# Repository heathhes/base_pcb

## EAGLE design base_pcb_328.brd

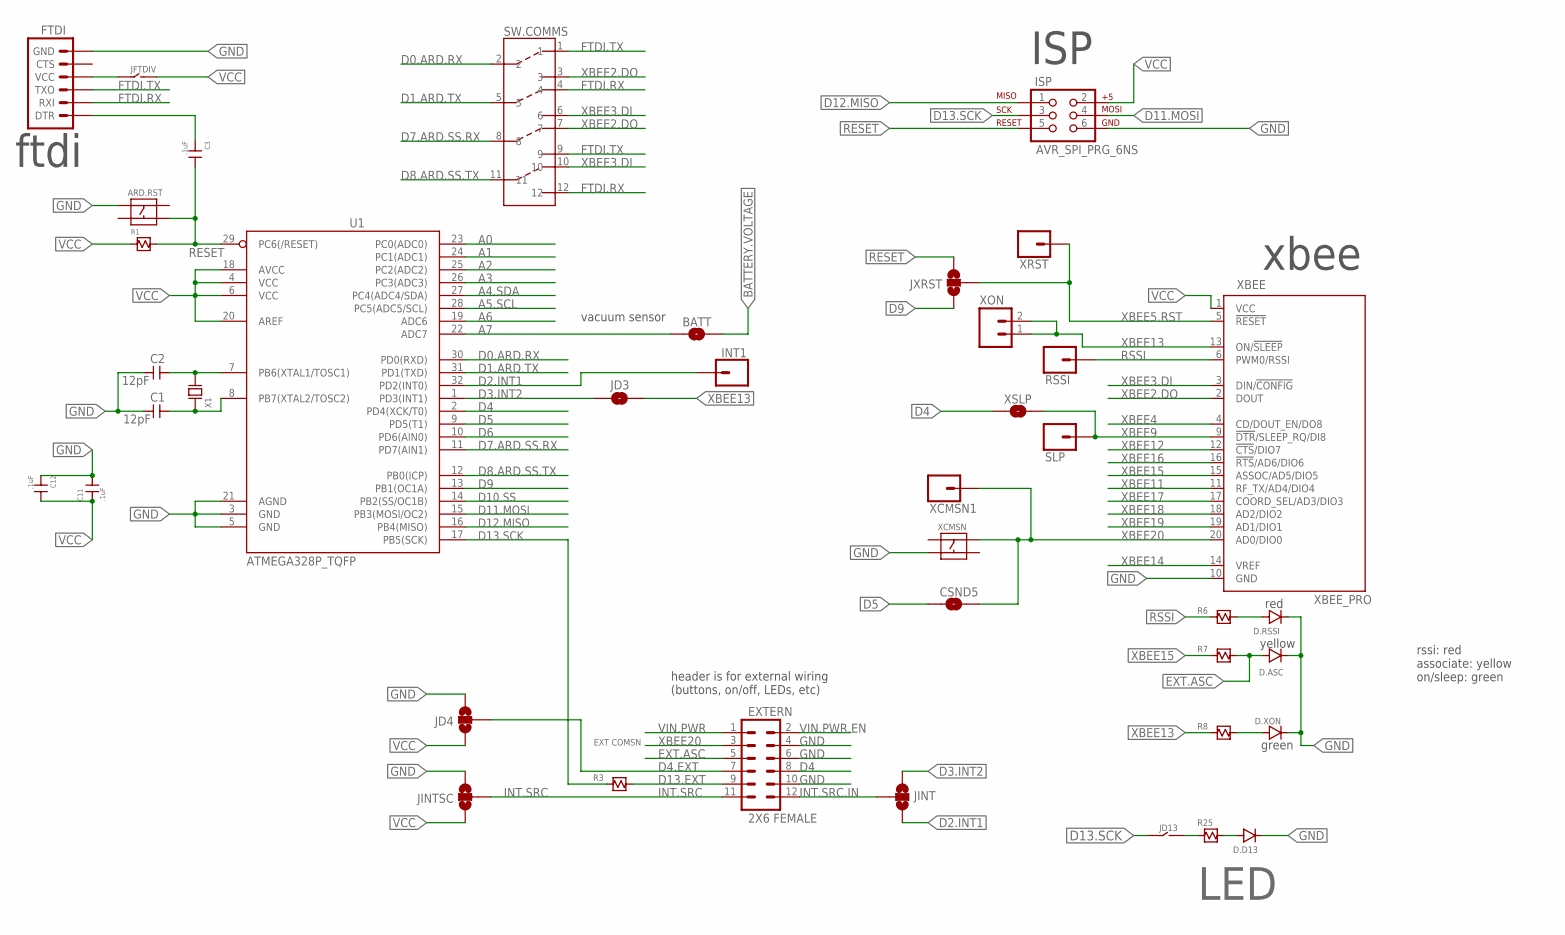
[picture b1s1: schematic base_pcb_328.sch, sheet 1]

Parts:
ARD.RST: C&K_PUSHBUTTON_SMALL_MOM_SPST_SMD; C&K_PUSHBUTTON_MOM_SMALL_SPST_SMD
BATT: JUMPER-PAD-2-NOYES_SILK; PAD-JUMPER-2-NO_YES_SILK
C1, C2: 12pF; 0603_CAPACITOR
C3: .1uF; 0603_CAPACITOR
C11, C12: .1uF; 0402_CAPACITOR
CSND5: JUMPER-PAD-2-NOYES_SILK; PAD-JUMPER-2-NO_YES_SILK
D.ASC, D.D13, D.RSSI, D.XON: 0603_LED
EXTERN: 2X6 FEMALE; 2X6
FTDI: ARDUINO_SERIAL_PROGRAMPTH; 1X06
INT1: M01PTH; 1X01
ISP: AVR_SPI_PRG_6NS; 2X3-NS
JD3: JUMPER-PAD-2-NOYES_SILK; PAD-JUMPER-2-NO_YES_SILK
JD4: JUMPER-PAD-3-NOYES_SILK; PAD-JUMPER-3-NO_YES_SILK
JD13: JUMPER_2WAY_.1"_TH
JFTDIV: JUMPER_2WAY_.1"_TH
JINT: JUMPER-PAD-3-NOYES_SILK; PAD-JUMPER-3-NO_YES_SILK
JINTSC: JUMPER-PAD-3-NOYES_SILK; PAD-JUMPER-3-NO_YES_SILK
JXRST: JUMPER-PAD-3-NOYES_SILK; PAD-JUMPER-3-NO_YES_SILK
R1, R3, R6, R7, R8, R25: 0603_RESISTOR
RSSI: M01PTH; 1X01
SLP: M01PTH; 1X01
SW.COMMS: COPAL_4PDT_SLIDE_SWITCH_TH; COPAL_4PDT_SLIDE_SWITCH
U1: ATMEGA328P_TQFP; TQFP32-08
X1: ABRACON_ABM3-16.000MHZ-D2Y-T_OSCILLATOR
XBEE: XBEE_PRO
XCMSN: C&K_PUSHBUTTON_SMALL_MOM_SPST_SMD; C&K_PUSHBUTTON_MOM_SMALL_SPST_SMD
XCMSN1: M01PTH; 1X01
XON: M02PTH; 1X02
XRST: M01PTH; 1X01
XSLP: JUMPER-PAD-2-NOYES_SILK; PAD-JUMPER-2-NO_YES_SILK

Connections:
A0: U1.23 (PC0(ADC0)); also elsewhere on the board
A1: U1.24 (PC1(ADC1)); also elsewhere on the board
A2: U1.25 (PC2(ADC2)); also elsewhere on the board
A3: U1.26 (PC3(ADC3)); also elsewhere on the board
A4.SDA: U1.27 (PC4(ADC4/SDA)); also elsewhere on the board
A5.SCL: U1.28 (PC5(ADC5/SCL)); also elsewhere on the board
A6: U1.19 (ADC6); also elsewhere on the board
A7: BATT.1, U1.22 (ADC7)
BATTERY.VOLTAGE: BATT.2; also elsewhere on the board
D0.ARD.RX: SW.COMMS.2, U1.30 (PD0(RXD))
D1.ARD.TX: SW.COMMS.5, U1.31 (PD1(TXD))
D2.INT1: INT1.1, JINT.3, U1.32 (PD2(INT0)); also elsewhere on the board
D3.INT2: JD3.1, JINT.1, U1.1 (PD3(INT1)); also elsewhere on the board
D4: EXTERN.8, U1.2 (PD4(XCK/T0)), XSLP.1; also elsewhere on the board
D4.EXT: EXTERN.7, JD4.2
D5: CSND5.1, U1.9 (PD5(T1)); also elsewhere on the board
D6: U1.10 (PD6(AIN0)); also elsewhere on the board
D7.ARD.SS.RX: SW.COMMS.8, U1.11 (PD7(AIN1))
D8.ARD.SS.TX: SW.COMMS.11, U1.12 (PB0(ICP)); also elsewhere on the board
D9: JXRST.1, U1.13 (PB1(OC1A)); also elsewhere on the board
D10.SS: U1.14 (PB2(SS/OC1B)); also elsewhere on the board
D11.MOSI: ISP.4, U1.15 (PB3(MOSI/OC2)); also elsewhere on the board
D12.MISO: ISP.1, U1.16 (PB4(MISO)); also elsewhere on the board
D13.EXT: EXTERN.9, R3.2
D13.SCK: ISP.3, JD13.P$1, R3.1, U1.17 (PB5(SCK)); also elsewhere on the board
EXT.ASC: D.ASC.1, EXTERN.5, R7.2
FTDI.RX: FTDI.2 (RXI), SW.COMMS.4, SW.COMMS.12
FTDI.TX: FTDI.3 (TXO), SW.COMMS.1, SW.COMMS.9
GND: ARD.RST.1, C1.2, C2.2, C11.2, C12.1, D.ASC.2, D.D13.2, D.RSSI.2, D.XON.2, EXTERN.4, EXTERN.6, EXTERN.10, FTDI.6 (GND), ISP.6, JD4.3, JINTSC.3, U1.3 (GND), U1.5 (GND), U1.21 (AGND), XBEE.10 (GND), XCMSN.3; also elsewhere on the board
INT.SRC: EXTERN.11, JINTSC.2
INT.SRC.IN: EXTERN.12, JINT.2
unnamed: C2.1, U1.7 (PB6(XTAL1/TOSC1)), X1.P$2 (2)
unnamed: C1.1, U1.8 (PB7(XTAL2/TOSC2)), X1.P$1 (1)
unnamed: C3.1, FTDI.1 (DTR)
unnamed: D.D13.1, R25.2
unnamed: JD13.P$2, R25.1
unnamed: D.RSSI.1, R6.2
unnamed: D.XON.1, R8.2
RESET: ARD.RST.4, C3.2, ISP.5, JXRST.3, R1.2, U1.29 (PC6(/RESET))
RSSI: R6.1, RSSI.1, XBEE.6 (PWM0/RSSI); also elsewhere on the board
VCC: C11.1, C12.2, ISP.2, JD4.1, JFTDIV.P$2, JINTSC.1, R1.1, U1.4 (VCC), U1.6 (VCC), U1.18 (AVCC), U1.20 (AREF), XBEE.1 (VCC); also elsewhere on the board
VCC.FTDI: FTDI.4 (VCC), JFTDIV.P$1
VIN.PWR: EXTERN.1; also elsewhere on the board
VIN.PWR.EN: EXTERN.2; also elsewhere on the board
XBEE2.DO: SW.COMMS.3, SW.COMMS.7, XBEE.2 (DOUT); also elsewhere on the board
XBEE3.DI: SW.COMMS.6, SW.COMMS.10, XBEE.3 (DIN/!CONFIG); also elsewhere on the board
XBEE4: XBEE.4 (CD/DOUT_EN/DO8); also elsewhere on the board
XBEE5.RST: JXRST.2, XBEE.5 (!RESET), XRST.1; also elsewhere on the board
XBEE9: SLP.1, XBEE.9 (!DTR!/SLEEP_RQ/DI8), XSLP.2; also elsewhere on the board
XBEE11: XBEE.11 (RF_TX/AD4/DIO4); also elsewhere on the board
XBEE12: XBEE.12 (!CTS!/DIO7); also elsewhere on the board
XBEE13: JD3.2, R8.1, XBEE.13 (ON/!SLEEP), XON.1, XON.2; also elsewhere on the board
XBEE14: XBEE.14 (VREF); also elsewhere on the board
XBEE15: R7.1, XBEE.15 (ASSOC/AD5/DIO5); also elsewhere on the board
XBEE16: XBEE.16 (!RTS!/AD6/DIO6); also elsewhere on the board
XBEE17: XBEE.17 (COORD_SEL/AD3/DIO3); also elsewhere on the board
XBEE18: XBEE.18 (AD2/DIO2); also elsewhere on the board
XBEE19: XBEE.19 (AD1/DIO1); also elsewhere on the board
XBEE20: CSND5.2, EXTERN.3, XBEE.20 (AD0/DIO0), XCMSN.2, XCMSN1.1; also elsewhere on the board

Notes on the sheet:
ISP
xbee
ftdi
vacuum sensor
LED
rssi: red associate: yellow on/sleep: green
red
green
yellow
header is for external wiring (buttons, on/off, LEDs, etc)
EXT COMSN

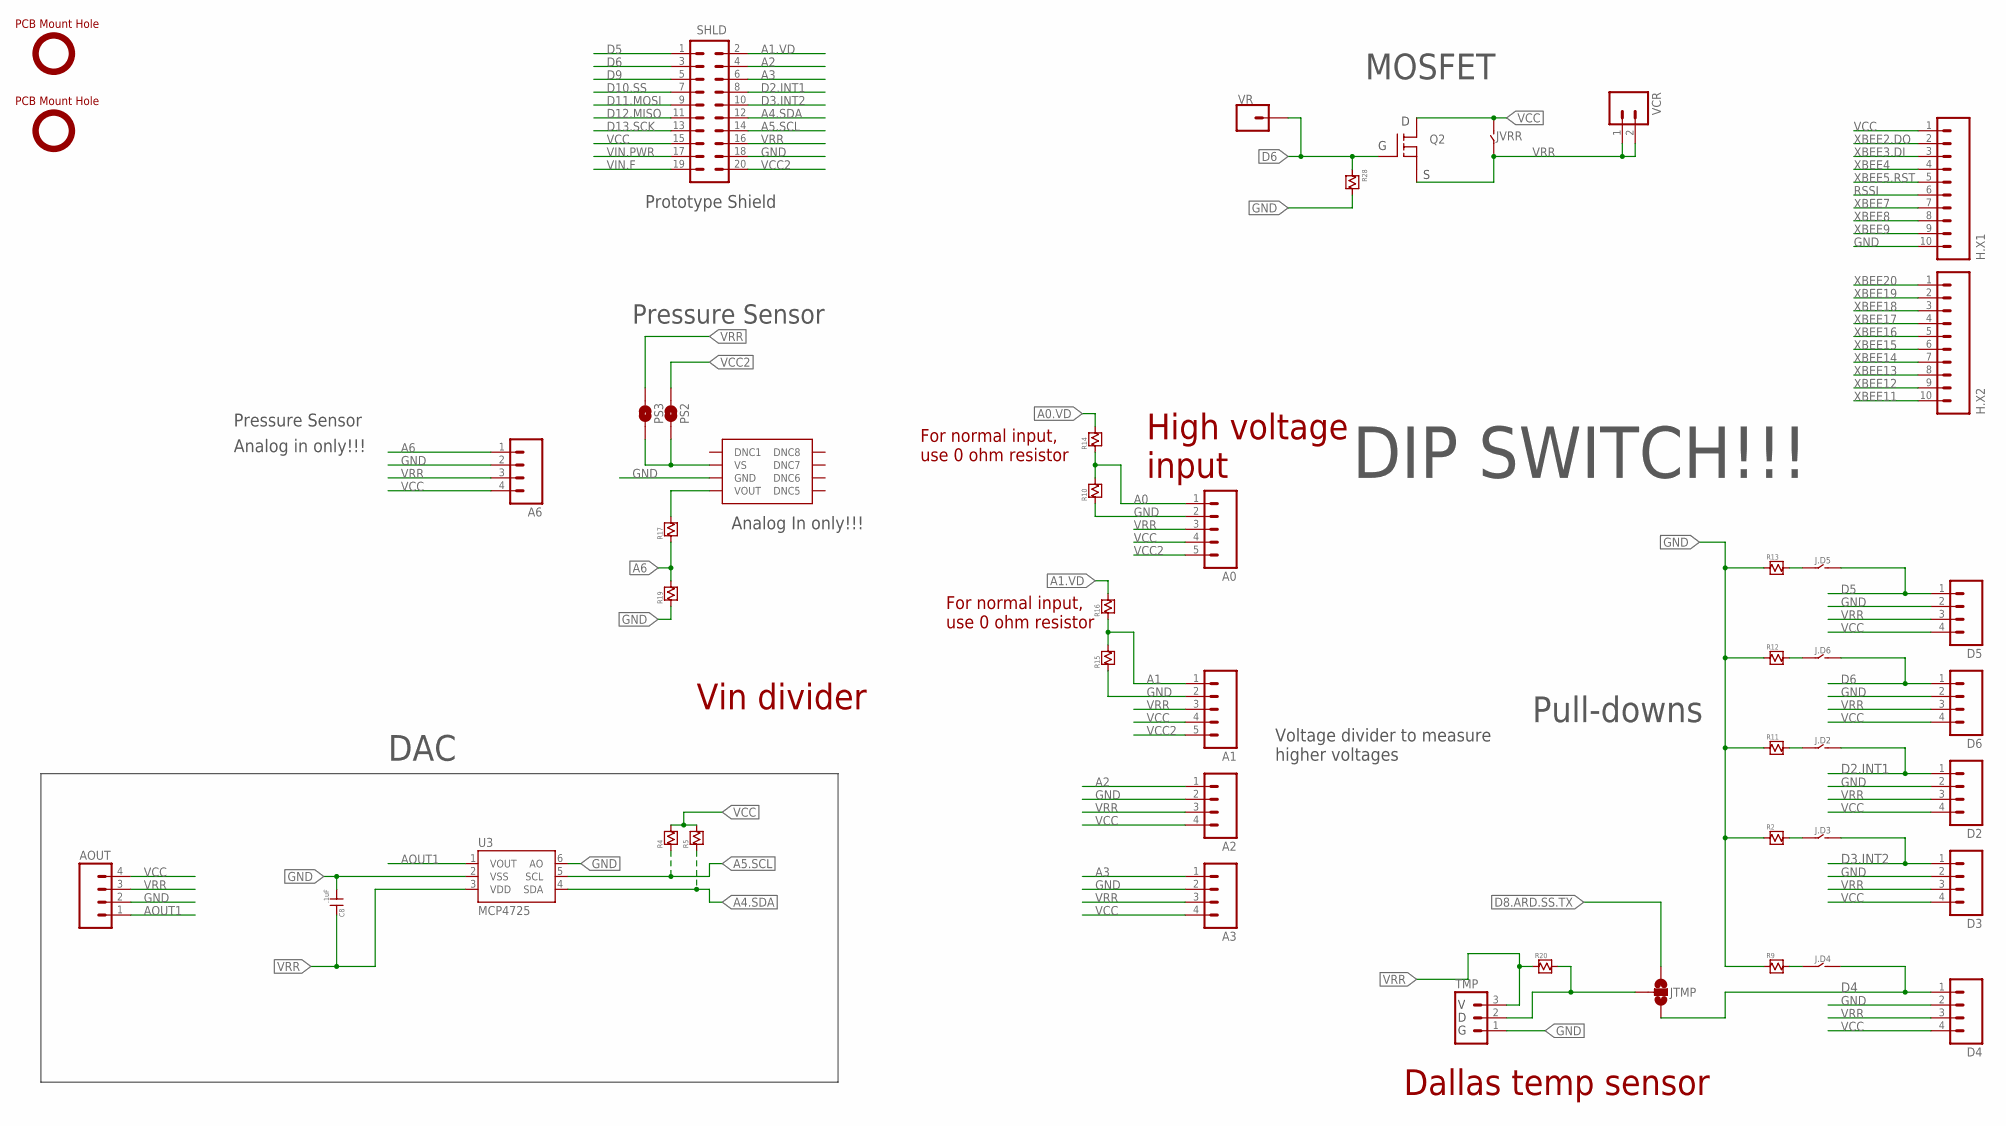
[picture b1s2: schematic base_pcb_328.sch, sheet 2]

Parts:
A0, A1: M05PTH; 1X05
A2, A3, A6: M04PTH; 1X04
AOUT: M04PTH; 1X04
C8: .1uF; 0603_CAPACITOR
D2, D3, D4, D5, D6: M04PTH; 1X04
H.X1, H.X2: M10NO_SILK_PTH_FEMALE; 1X10_NO_SILK
J.D2, J.D3, J.D4, J.D5, J.D6: JUMPER_2WAY_.1"_TH
JTMP: JUMPER-PAD-3-NOYES_SILK; PAD-JUMPER-3-NO_YES_SILK
JVRR: JUMPER_2WAY_.1"_TH
PS2, PS3: JUMPER-PAD-2-NOYES_SILK; PAD-JUMPER-2-NO_YES_SILK
Q2: INFINEON_MOSFET_NCH; INFINEON_MOSFET_NCH_SMD
R2, R4, R5, R9, R10, R11, R12, R13, R14, R15, R16, R17, R19, R20, R28: 0603_RESISTOR
SHLD: M10X2; 2X10
TMP: M03PTH; 1X03
U3: MCP4725; SOT23-6
U$9: MPXV6115VC6U
U$13, U$14: PCB_HOLE
VCR: M02PTH; 1X02
VR: M01PTH; 1X01

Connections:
A0: A0.1, R10.2, R14.1; also elsewhere on the board
A0.VD: R14.2; also elsewhere on the board
A1: A1.1, R15.2, R16.1; also elsewhere on the board
A1.VD: R16.2, SHLD.2
A2: A2.1, SHLD.4; also elsewhere on the board
A3: A3.1, SHLD.6; also elsewhere on the board
A4.SDA: R5.1, SHLD.12, U3.4 (SDA); also elsewhere on the board
A5.SCL: R4.1, SHLD.14, U3.5 (SCL); also elsewhere on the board
A6: A6.1, R17.1, R19.2; also elsewhere on the board
A6.IN: R17.2, U$9.4 (VOUT)
AOUT1: AOUT.1, U3.1 (VOUT)
D2.INT1: D2.1, J.D2.P$2, SHLD.8; also elsewhere on the board
D3.INT2: D3.1, J.D3.P$2, SHLD.10; also elsewhere on the board
D4: D4.1, J.D4.P$2, JTMP.3; also elsewhere on the board
D5: D5.1, J.D5.P$2, SHLD.1; also elsewhere on the board
D6: D6.1, J.D6.P$2, Q2.G, R28.1, SHLD.3, VR.1; also elsewhere on the board
D8.ARD.SS.TX: JTMP.1; also elsewhere on the board
D9: SHLD.5; also elsewhere on the board
D10.SS: SHLD.7; also elsewhere on the board
D11.MOSI: SHLD.9; also elsewhere on the board
D12.MISO: SHLD.11; also elsewhere on the board
D13.SCK: SHLD.13; also elsewhere on the board
GND: A0.2, A1.2, A2.2, A3.2, A6.2, AOUT.2, C8.1, D2.2, D3.2, D4.2, D5.2, D6.2, H.X1.10, R2.1, R9.1, R10.1, R11.1, R12.1, R13.1, R15.1, R19.1, R28.2, SHLD.18, TMP.1, U3.2 (VSS), U3.6 (AO), U$9.3 (GND); also elsewhere on the board
unnamed: JTMP.2, R20.2, TMP.2
unnamed: PS2.1, PS3.1, U$9.2 (VS)
unnamed: J.D3.P$1, R2.2
unnamed: J.D6.P$1, R12.2
unnamed: J.D5.P$1, R13.2
unnamed: J.D2.P$1, R11.2
unnamed: J.D4.P$1, R9.2
RSSI: H.X1.6; also elsewhere on the board
VCC: A0.4, A1.4, A2.4, A3.4, A6.4, AOUT.4, D2.4, D3.4, D4.4, D5.4, D6.4, H.X1.1, JVRR.P$2, Q2.D, R4.2, R5.2, SHLD.15; also elsewhere on the board
VCC2: A0.5, A1.5, PS2.2, SHLD.20; also elsewhere on the board
VIN.F: SHLD.19; also elsewhere on the board
VIN.PWR: SHLD.17; also elsewhere on the board
VRR: A0.3, A1.3, A2.3, A3.3, A6.3, AOUT.3, C8.2, D2.3, D3.3, D4.3, D5.3, D6.3, JVRR.P$1, PS3.2, Q2.S, R20.1, SHLD.16, TMP.3, U3.3 (VDD), VCR.1, VCR.2; also elsewhere on the board
XBEE2.DO: H.X1.2; also elsewhere on the board
XBEE3.DI: H.X1.3; also elsewhere on the board
XBEE4: H.X1.4; also elsewhere on the board
XBEE5.RST: H.X1.5; also elsewhere on the board
XBEE7: H.X1.7
XBEE8: H.X1.8
XBEE9: H.X1.9; also elsewhere on the board
XBEE11: H.X2.10; also elsewhere on the board
XBEE12: H.X2.9; also elsewhere on the board
XBEE13: H.X2.8; also elsewhere on the board
XBEE14: H.X2.7; also elsewhere on the board
XBEE15: H.X2.6; also elsewhere on the board
XBEE16: H.X2.5; also elsewhere on the board
XBEE17: H.X2.4; also elsewhere on the board
XBEE18: H.X2.3; also elsewhere on the board
XBEE19: H.X2.2; also elsewhere on the board
XBEE20: H.X2.1; also elsewhere on the board

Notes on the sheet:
MOSFET
DAC
Analog In only!!!
Prototype Shield
Pressure Sensor
Voltage divider to measure higher voltages
Analog in only!!!
Pull-downs
Dallas temp sensor
Vin divider
High voltage input
For normal input, use 0 ohm resistor
DIP SWITCH!!!

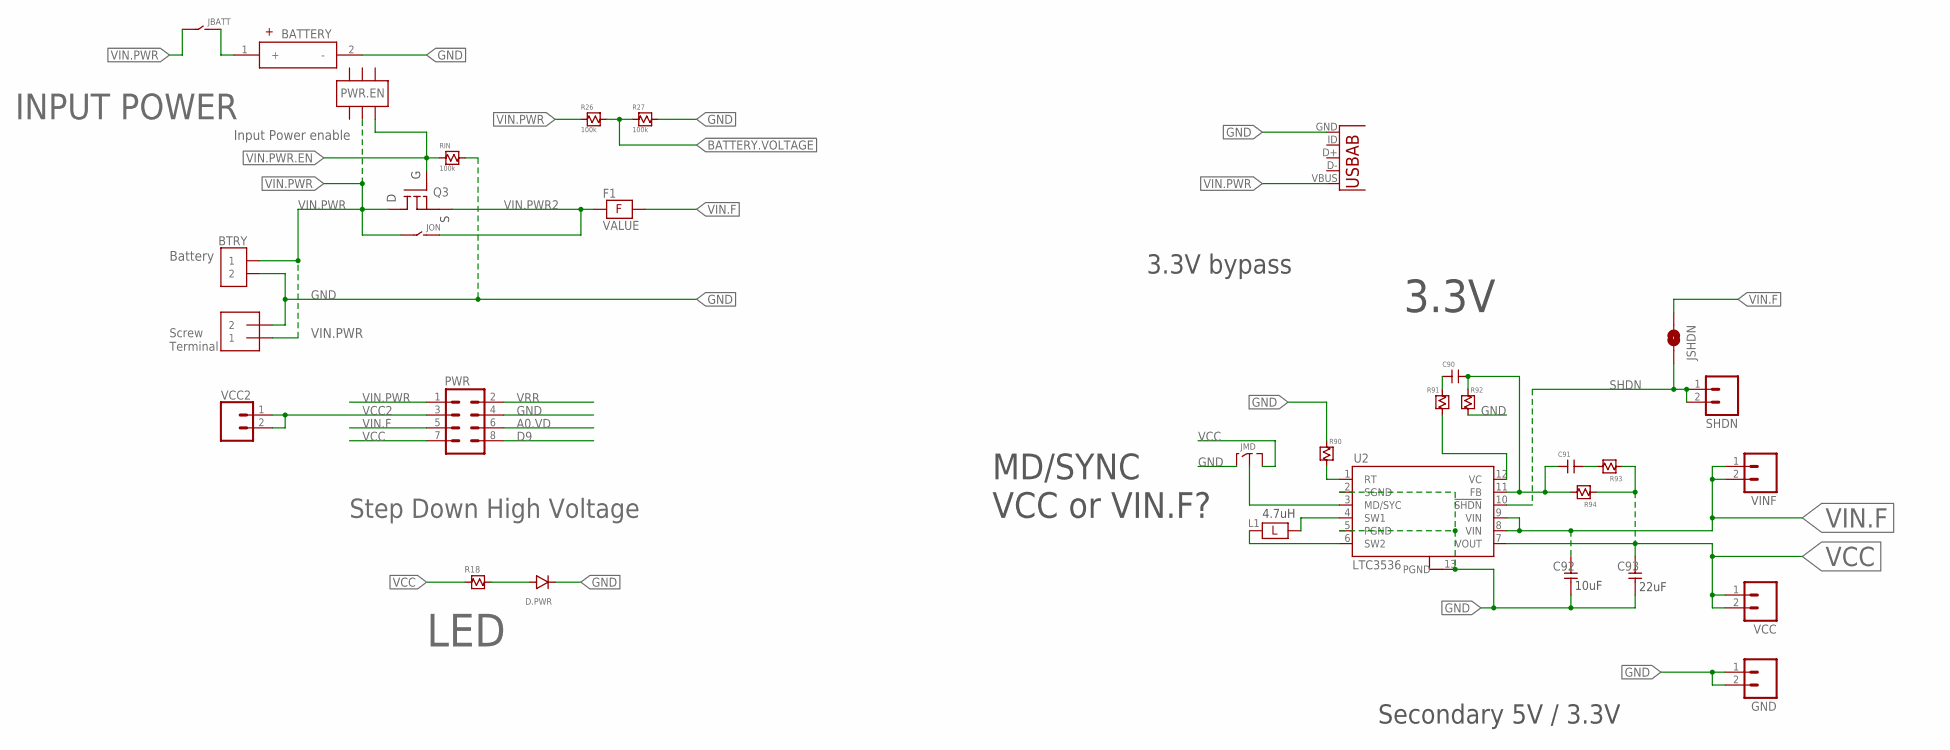
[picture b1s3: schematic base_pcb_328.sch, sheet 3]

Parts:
5V: USB-AB; USB-AB-MICRO-SMD
BATTERY: BATTERY_HOLDER_18650
BTRY: MOLEX_2PIN_LOCKING_TH
C90, C91: 0603_CAPACITOR
C92: 10uF; 0805_CAPACITOR
C93: 22uF; 0805_CAPACITOR
D.PWR: 0603_LED
F1: PTC_FUSE_PTC_1206; BEL_FUSE_PTC_FUSE_1206
GND: M02PTH; 1X02
INPUT.PWR: 1X2-3.5MM
JBATT: JUMPER_2WAY_.1"_TH
JMD: JUMPER_3WAY_.1"_TH
JON: JUMPER_2WAY_.1"_TH
JSHDN: JUMPER-PAD-2-NOYES_SILK; PAD-JUMPER-2-NO_YES_SILK
L1: 4.7uH; BOURNS_INDUCTOR_SMD
PWR: M04X2; 2X4
PWR.EN: C&K_DPDT_SLIDE_SWITCH_SMD_HIDDEN_PADS; C&K_SLIDE_SWITCH_DPDT_SMD_HIDDEN_PADS
Q3: INFINEON_MOSFET_NCH; INFINEON_MOSFET_NCH_SMD
R18, R90, R91, R92, R93, R94: 0603_RESISTOR
R26, R27: 100k; 0603_RESISTOR
RIN: 100k; 0603_RESISTOR
SHDN: M02PTH; 1X02
U2: LTC3536_ADJ_12PIN
VCC, VCC2: M02PTH; 1X02
VINF: M02PTH; 1X02

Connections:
A0.VD: PWR.6; also elsewhere on the board
BATTERY.VOLTAGE: R26.2, R27.1; also elsewhere on the board
D9: PWR.8; also elsewhere on the board
GND: 5V.GND, BATTERY.2 (-), BTRY.2, C92.1, C93.1, D.PWR.2, GND.1, GND.2, INPUT.PWR.2, JMD.P$3, PWR.4, R27.2, R90.2, R92.1, RIN.2, U2.2 (SGND), U2.5 (PGND), U2.13 (PGND); also elsewhere on the board
unnamed: BATTERY.1 (+), JBATT.P$2
unnamed: L1.P$2, U2.4 (SW1)
unnamed: D.PWR.1, R18.2
unnamed: L1.P$1, U2.6 (SW2)
unnamed: R90.1, U2.1 (RT)
unnamed: C90.2, C91.1, R92.2, R94.2, U2.11 (FB)
unnamed: C90.1, R91.2
unnamed: R91.1, U2.12 (VC)
unnamed: C91.2, R93.2
unnamed: JMD.P$2, U2.3 (MD/SYC)
SHDN: JSHDN.2, SHDN.1, SHDN.2, U2.10 (!SHDN)
VCC: C93.2, JMD.P$1, PWR.7, R18.1, R93.1, R94.1, U2.7 (VOUT), VCC.1, VCC.2; also elsewhere on the board
VCC2: PWR.3, VCC2.1, VCC2.2; also elsewhere on the board
VIN.F: C92.2, F1.P$2, JSHDN.1, PWR.5, U2.8 (VIN), U2.9 (VIN), VINF.1, VINF.2; also elsewhere on the board
VIN.PWR: 5V.VBUS, BTRY.1, INPUT.PWR.1, JBATT.P$1, JON.P$1, PWR.1, PWR.EN.5, Q3.D, R26.1; also elsewhere on the board
VIN.PWR2: F1.P$1, JON.P$2, Q3.S
VIN.PWR.EN: PWR.EN.4, Q3.G, RIN.1; also elsewhere on the board
VRR: PWR.2; also elsewhere on the board

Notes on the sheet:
4.7uH
INPUT POWER
Battery
Input Power enable
Screw Terminal
Step Down High Voltage
LED
3.3V
3.3V bypass
Secondary 5V / 3.3V
MD/SYNC VCC or VIN.F?
BATTERY

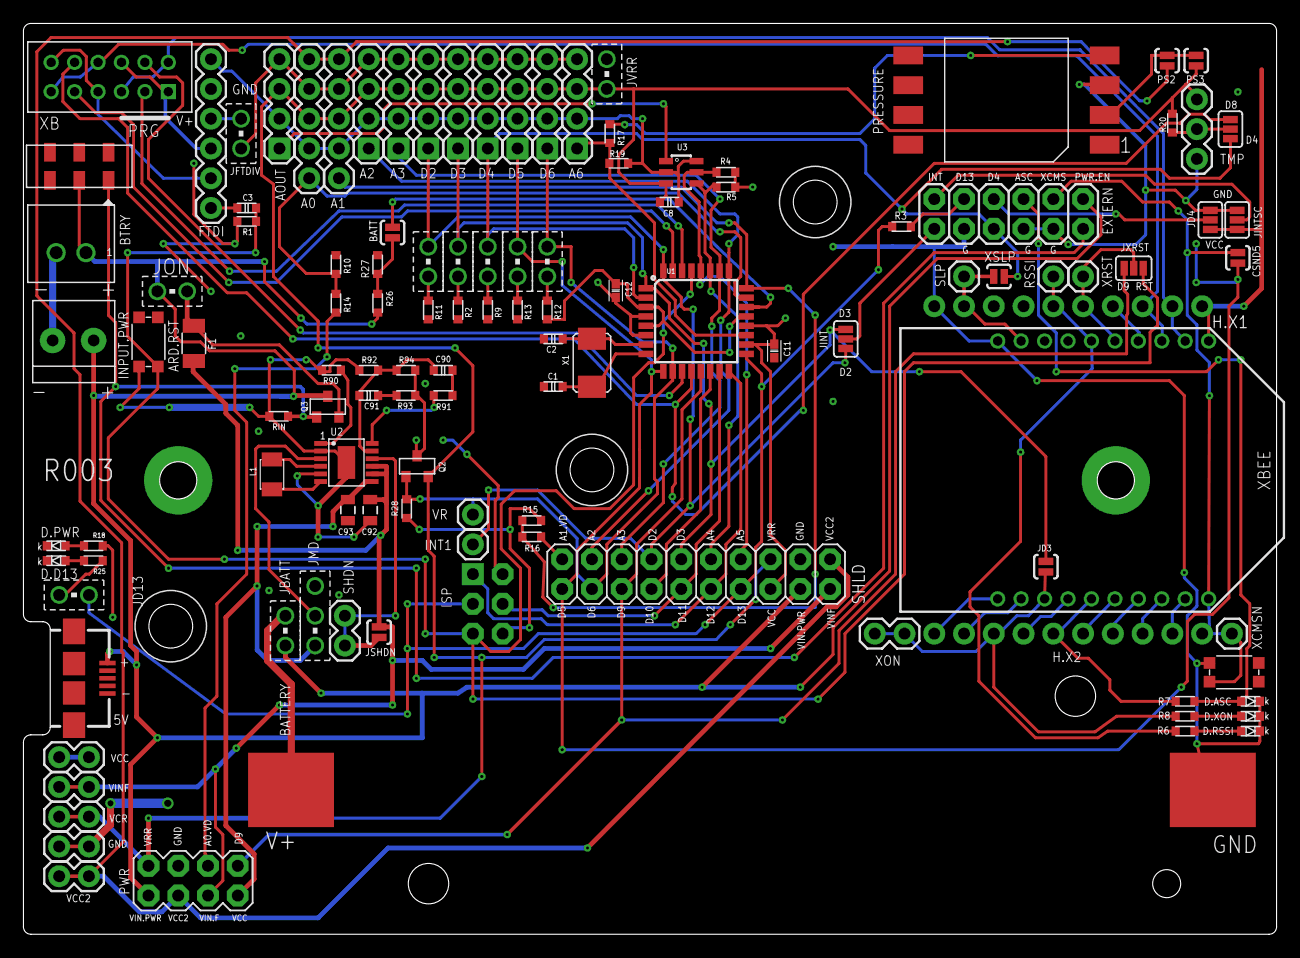
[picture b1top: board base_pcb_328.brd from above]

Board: 2 copper layers, 106.9 x 77.7 mm, 123 parts (0 on the bottom side), 85 nets.

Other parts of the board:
U$1: POLYCASE_WH_02
U$2: PEM_2-56
U$8: BASE328_SHIELD_1

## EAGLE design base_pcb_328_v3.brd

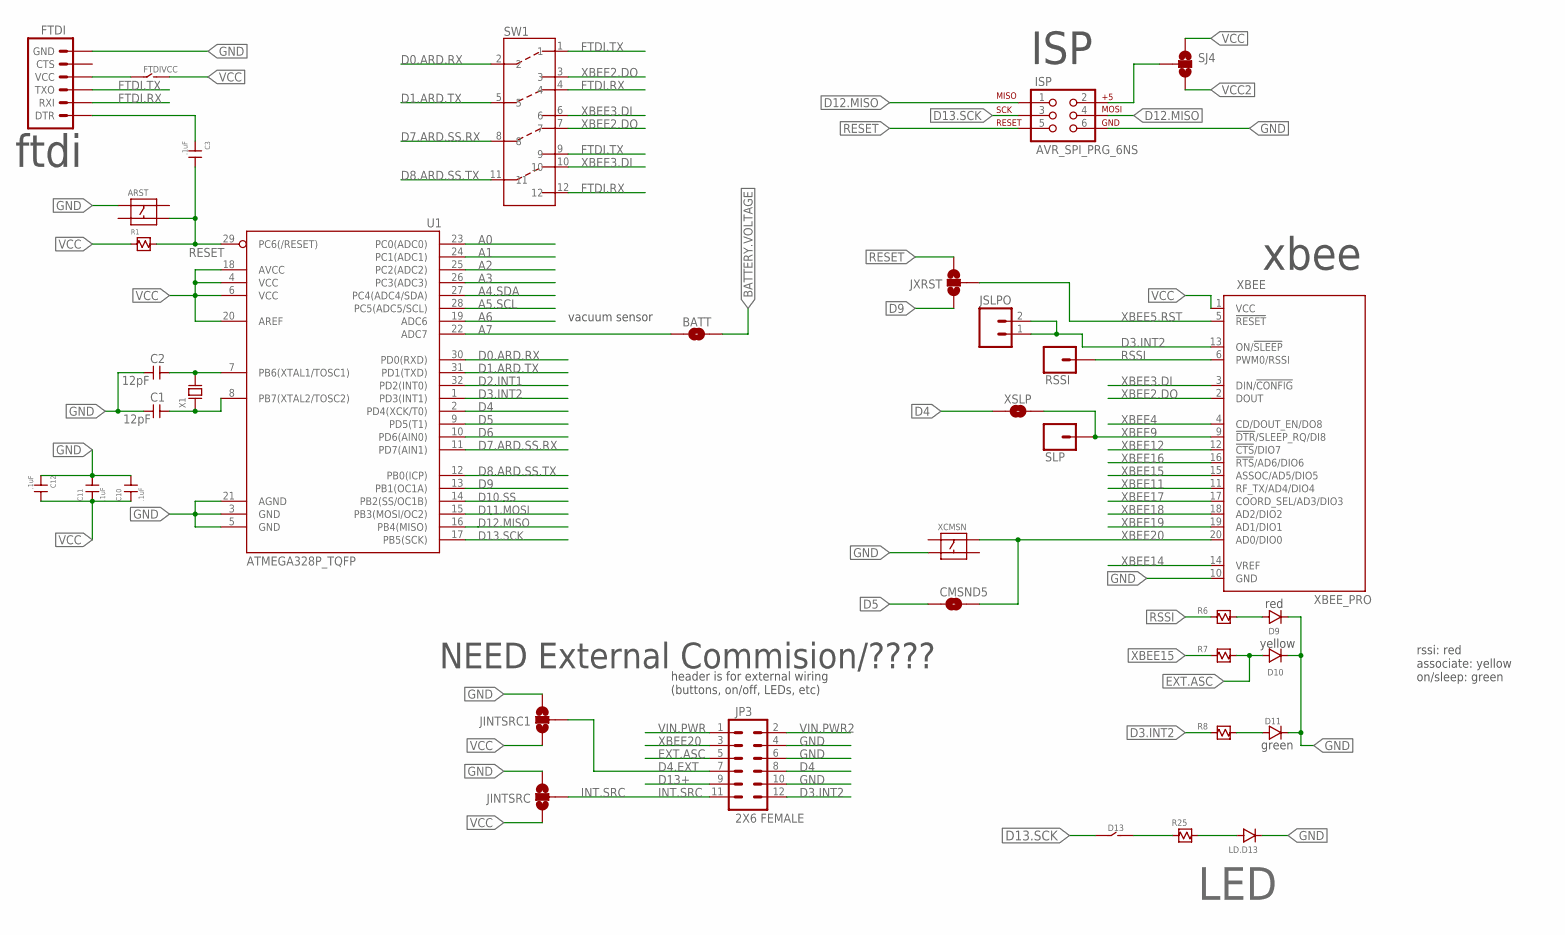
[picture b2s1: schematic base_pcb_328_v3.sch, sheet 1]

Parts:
ARST: C&K_PUSHBUTTON_SMALL_MOM_SPST_SMD; C&K_PUSHBUTTON_MOM_SMALL_SPST_SMD
BATT: JUMPER-PAD-2-NOYES_SILK; PAD-JUMPER-2-NO_YES_SILK
C1, C2: 12pF; 0603_CAPACITOR
C3: .1uF; 0603_CAPACITOR
C10, C11, C12: .1uF; 0402_CAPACITOR
CMSND5: JUMPER-PAD-2-NOYES_SILK; PAD-JUMPER-2-NO_YES_SILK
D9, D10, D11: 0603_LED
D13: JUMPER_2WAY_.1"_TH
FTDI: ARDUINO_SERIAL_PROGRAMPTH; 1X06
FTDIVCC: JUMPER_2WAY_.1"_TH
ISP: AVR_SPI_PRG_6NS; 2X3-NS
JINTSRC, JINTSRC1: JUMPER-PAD-3-NOYES_SILK; PAD-JUMPER-3-NO_YES_SILK
JP3: 2X6 FEMALE; 2X6
JSLPO: M02PTH; 1X02
JXRST: JUMPER-PAD-3-NOYES_SILK; PAD-JUMPER-3-NO_YES_SILK
LD.D13: 0603_LED
R1, R6, R7, R8, R25: 0603_RESISTOR
RSSI: M01PTH; 1X01
SJ4: JUMPER-PAD-3-NOYES_SILK; PAD-JUMPER-3-NO_YES_SILK
SLP: M01PTH; 1X01
SW1: COPAL_4PDT_SLIDE_SWITCH_TH; COPAL_4PDT_SLIDE_SWITCH
U1: ATMEGA328P_TQFP; TQFP32-08
X1: ABRACON_ABM3-16.000MHZ-D2Y-T_OSCILLATOR
XBEE: XBEE_PRO
XCMSN: C&K_PUSHBUTTON_SMALL_MOM_SPST_SMD; C&K_PUSHBUTTON_MOM_SMALL_SPST_SMD
XSLP: JUMPER-PAD-2-NOYES_SILK; PAD-JUMPER-2-NO_YES_SILK

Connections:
A0: U1.23 (PC0(ADC0)); also elsewhere on the board
A1: U1.24 (PC1(ADC1)); also elsewhere on the board
A2: U1.25 (PC2(ADC2)); also elsewhere on the board
A3: U1.26 (PC3(ADC3)); also elsewhere on the board
A4.SDA: U1.27 (PC4(ADC4/SDA)); also elsewhere on the board
A5.SCL: U1.28 (PC5(ADC5/SCL)); also elsewhere on the board
A6: U1.19 (ADC6); also elsewhere on the board
A7: BATT.1, U1.22 (ADC7)
BATTERY.VOLTAGE: BATT.2; also elsewhere on the board
D0.ARD.RX: SW1.2, U1.30 (PD0(RXD))
D1.ARD.TX: SW1.5, U1.31 (PD1(TXD))
D2.INT1: U1.32 (PD2(INT0)); also elsewhere on the board
D3.INT2: JP3.12, JSLPO.1, JSLPO.2, R8.1, U1.1 (PD3(INT1)), XBEE.13 (ON/!SLEEP); also elsewhere on the board
D4: JP3.8, U1.2 (PD4(XCK/T0)), XSLP.1; also elsewhere on the board
D4.EXT: JINTSRC1.2, JP3.7
D5: CMSND5.1, U1.9 (PD5(T1)); also elsewhere on the board
D6: U1.10 (PD6(AIN0)); also elsewhere on the board
D7.ARD.SS.RX: SW1.8, U1.11 (PD7(AIN1))
D8.ARD.SS.TX: SW1.11, U1.12 (PB0(ICP))
D9: JXRST.1, U1.13 (PB1(OC1A)); also elsewhere on the board
D10.SS: U1.14 (PB2(SS/OC1B)); also elsewhere on the board
D11.MOSI: U1.15 (PB3(MOSI/OC2)); also elsewhere on the board
D12.MISO: ISP.1, ISP.4, U1.16 (PB4(MISO)); also elsewhere on the board
D13+: JP3.9
D13.SCK: D13.P$1, ISP.3, U1.17 (PB5(SCK)); also elsewhere on the board
EXT.ASC: D10.1, JP3.5, R7.2
FTDI.RX: FTDI.2 (RXI)
FTDI.TX: FTDI.3 (TXO)
GND: ARST.1, C1.2, C2.2, C10.2, C11.2, C12.1, D9.2, D10.2, D11.2, FTDI.6 (GND), ISP.6, JINTSRC.3, JINTSRC1.3, JP3.4, JP3.6, JP3.10, LD.D13.2, U1.3 (GND), U1.5 (GND), U1.21 (AGND), XBEE.10 (GND), XCMSN.3; also elsewhere on the board
INT.SRC: JINTSRC.2, JP3.11
unnamed: C2.1, U1.7 (PB6(XTAL1/TOSC1)), X1.P$2 (2)
unnamed: C1.1, U1.8 (PB7(XTAL2/TOSC2)), X1.P$1 (1)
unnamed: C3.1, FTDI.1 (DTR)
unnamed: LD.D13.1, R25.2
unnamed: D13.P$2, R25.1
unnamed: ISP.2, SJ4.2
unnamed: D9.1, R6.2
unnamed: D11.1, R8.2
RESET: ARST.4, C3.2, ISP.5, JXRST.3, R1.2, U1.29 (PC6(/RESET))
RSSI: R6.1, RSSI.1, XBEE.6 (PWM0/RSSI); also elsewhere on the board
VCC: C10.1, C11.1, C12.2, FTDI.4 (VCC), FTDIVCC.P$1, FTDIVCC.P$2, JINTSRC.1, JINTSRC1.1, R1.1, SJ4.1, U1.4 (VCC), U1.6 (VCC), U1.18 (AVCC), U1.20 (AREF), XBEE.1 (VCC); also elsewhere on the board
VCC2: SJ4.3; also elsewhere on the board
VIN.PWR: JP3.1; also elsewhere on the board
VIN.PWR2: JP3.2; also elsewhere on the board
XBEE2.DO: XBEE.2 (DOUT); also elsewhere on the board
XBEE3.DI: XBEE.3 (DIN/!CONFIG); also elsewhere on the board
XBEE4: XBEE.4 (CD/DOUT_EN/DO8); also elsewhere on the board
XBEE5.RST: JXRST.2, XBEE.5 (!RESET); also elsewhere on the board
XBEE9: SLP.1, XBEE.9 (!DTR!/SLEEP_RQ/DI8), XSLP.2; also elsewhere on the board
XBEE11: XBEE.11 (RF_TX/AD4/DIO4); also elsewhere on the board
XBEE12: XBEE.12 (!CTS!/DIO7); also elsewhere on the board
XBEE14: XBEE.14 (VREF); also elsewhere on the board
XBEE15: R7.1, XBEE.15 (ASSOC/AD5/DIO5); also elsewhere on the board
XBEE16: XBEE.16 (!RTS!/AD6/DIO6); also elsewhere on the board
XBEE17: XBEE.17 (COORD_SEL/AD3/DIO3); also elsewhere on the board
XBEE18: XBEE.18 (AD2/DIO2); also elsewhere on the board
XBEE19: XBEE.19 (AD1/DIO1); also elsewhere on the board
XBEE20: CMSND5.2, JP3.3, XBEE.20 (AD0/DIO0), XCMSN.2; also elsewhere on the board

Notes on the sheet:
ISP
xbee
ftdi
vacuum sensor
LED
rssi: red associate: yellow on/sleep: green
red
green
yellow
header is for external wiring (buttons, on/off, LEDs, etc)
NEED External Commision/????

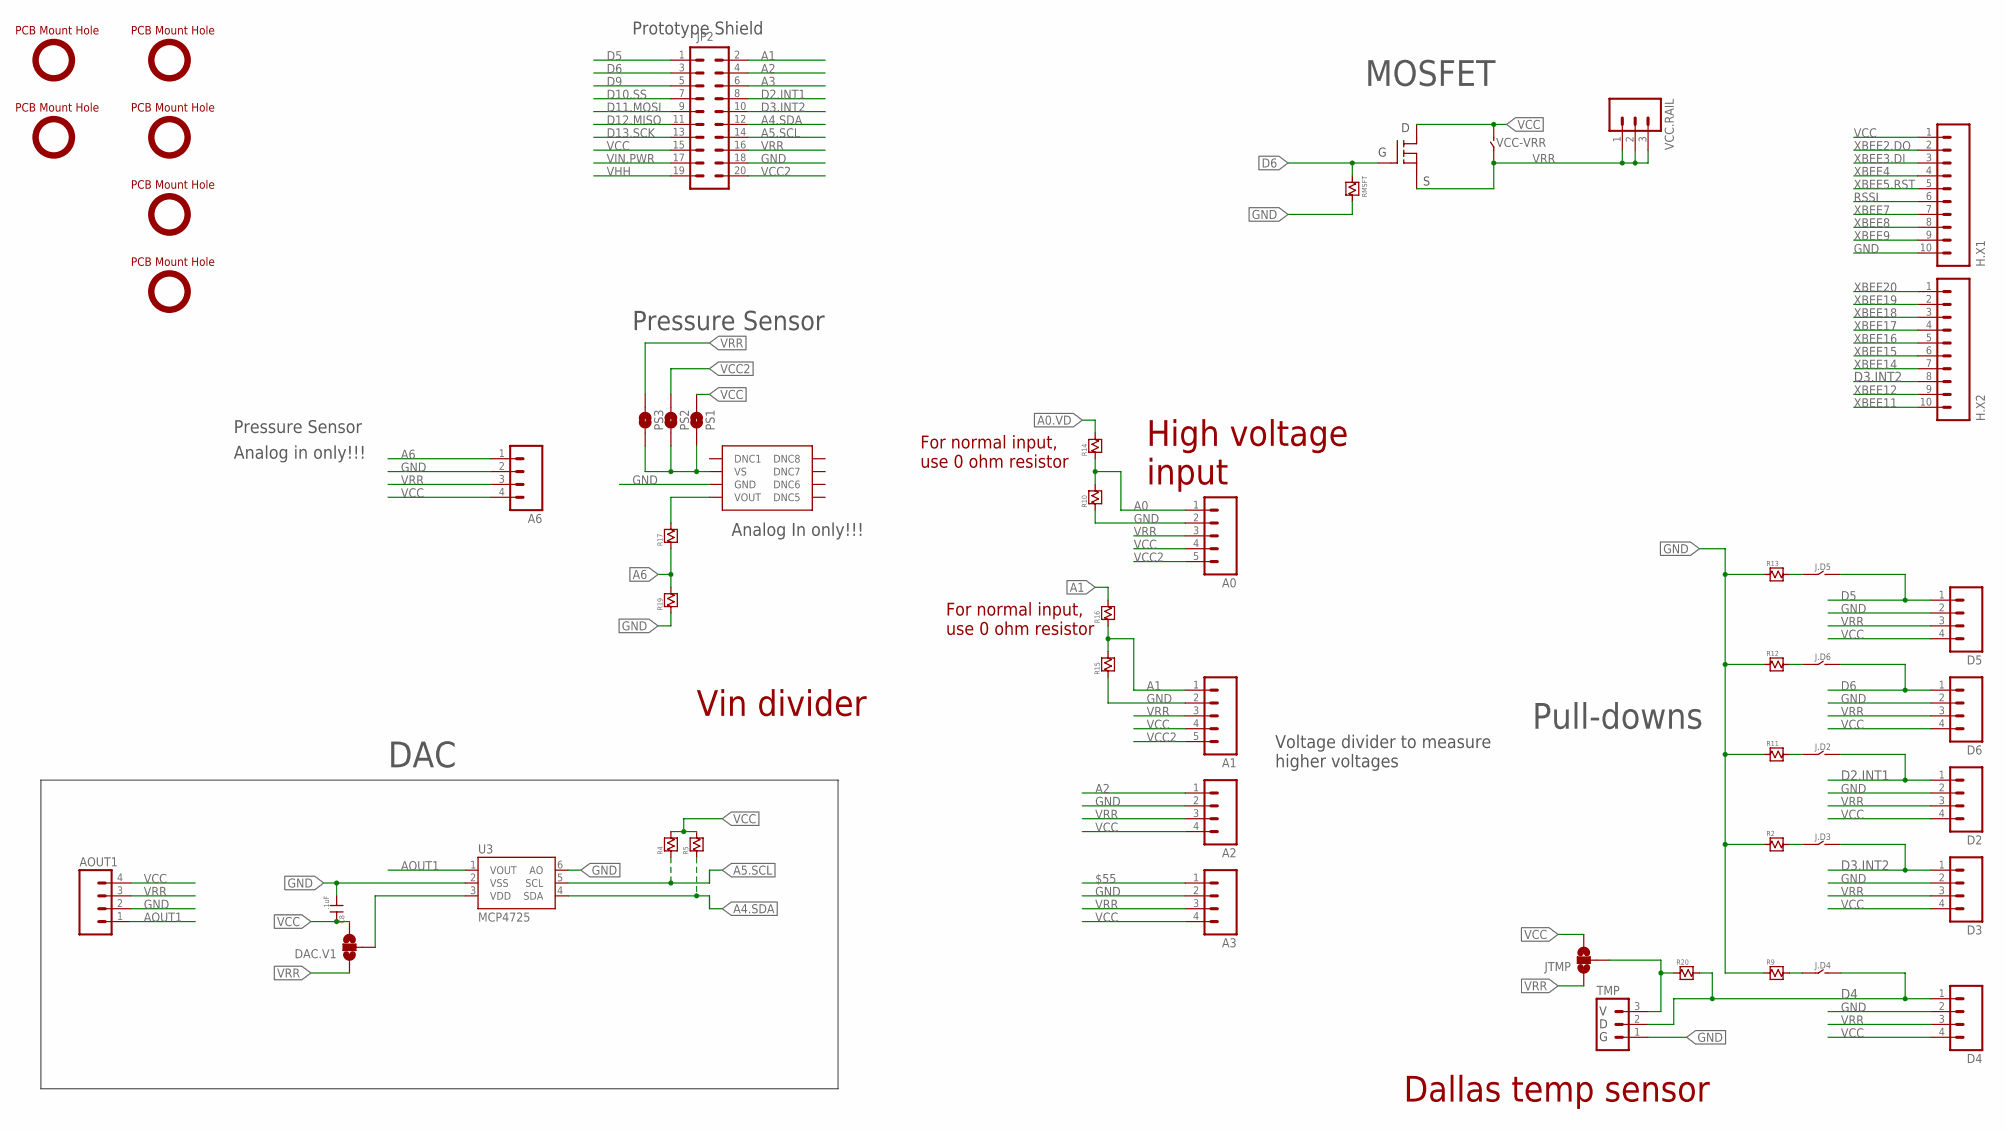
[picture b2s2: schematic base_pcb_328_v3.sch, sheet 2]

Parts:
A0, A1: M05PTH; 1X05
A2, A3, A6: M04PTH; 1X04
AOUT1: M04PTH; 1X04
C8: .1uF; 0603_CAPACITOR
D2, D3, D4, D5, D6: M04PTH; 1X04
DAC.V1: JUMPER-PAD-3-NOYES_SILK; PAD-JUMPER-3-NO_YES_SILK
H.X1, H.X2: M10NO_SILK_PTH_FEMALE; 1X10_NO_SILK
J.D2, J.D3, J.D4, J.D5, J.D6: JUMPER_2WAY_.1"_TH
JP2: M10X2; 2X10
JTMP: JUMPER-PAD-3-NOYES_SILK; PAD-JUMPER-3-NO_YES_SILK
PS1, PS2, PS3: JUMPER-PAD-2-NOYES_SILK; PAD-JUMPER-2-NO_YES_SILK
Q2: INFINEON_MOSFET_NCH; INFINEON_MOSFET_NCH_SMD
R2, R4, R5, R9, R10, R11, R12, R13, R14, R15, R16, R17, R19, R20: 0603_RESISTOR
RMSFT: 0603_RESISTOR
TMP: M03PTH; 1X03
U3: MCP4725; SOT23-6
U$2, U$4, U$5, U$6, U$13, U$14: PCB_HOLE
U$9: MPXV6115VC6U
VCC-VRR: JUMPER_2WAY_.1"_TH
VCC.RAIL: M03PTH; 1X03

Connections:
$55: A3.1
A0: A0.1, R10.2, R14.1; also elsewhere on the board
A0.VD: R14.2; also elsewhere on the board
A1: A1.1, JP2.2, R15.2, R16.1, R16.2; also elsewhere on the board
A2: A2.1, JP2.4; also elsewhere on the board
A3: JP2.6; also elsewhere on the board
A4.SDA: JP2.12, R5.1, U3.4 (SDA); also elsewhere on the board
A5.SCL: JP2.14, R4.1, U3.5 (SCL); also elsewhere on the board
A6: A6.1, R17.1, R19.2; also elsewhere on the board
A6.IN: R17.2, U$9.4 (VOUT)
AOUT1: AOUT1.1, U3.1 (VOUT)
D2.INT1: D2.1, J.D2.P$2, JP2.8; also elsewhere on the board
D3.INT2: D3.1, H.X2.8, J.D3.P$2, JP2.10; also elsewhere on the board
D4: D4.1, J.D4.P$2, R20.2, TMP.2; also elsewhere on the board
D5: D5.1, J.D5.P$2; also elsewhere on the board
D6: D6.1, J.D6.P$2, JP2.3, Q2.G, RMSFT.1; also elsewhere on the board
D9: JP2.5; also elsewhere on the board
D10.SS: JP2.7; also elsewhere on the board
D11.MOSI: JP2.9; also elsewhere on the board
D12.MISO: JP2.11; also elsewhere on the board
D13.SCK: JP2.13; also elsewhere on the board
GND: A0.2, A1.2, A2.2, A3.2, A6.2, AOUT1.2, C8.1, D2.2, D3.2, D4.2, D5.2, D6.2, H.X1.10, JP2.18, R2.1, R9.1, R10.1, R11.1, R12.1, R13.1, R15.1, R19.1, RMSFT.2, TMP.1, U3.2 (VSS), U3.6 (AO), U$9.3 (GND); also elsewhere on the board
unnamed: PS1.1, PS2.1, PS3.1, U$9.2 (VS)
unnamed: J.D3.P$1, R2.2
unnamed: J.D6.P$1, R12.2
unnamed: J.D5.P$1, R13.2
unnamed: J.D2.P$1, R11.2
unnamed: J.D4.P$1, R9.2
unnamed: JTMP.2, R20.1, TMP.3
RSSI: H.X1.6; also elsewhere on the board
VCC: A0.4, A1.4, A2.4, A3.4, A6.4, AOUT1.4, C8.2, D2.4, D3.4, D4.4, D5.4, D6.4, DAC.V1.2, DAC.V1.3, H.X1.1, JP2.15, JTMP.3, PS1.2, Q2.D, R4.2, R5.2, U3.3 (VDD), VCC-VRR.P$2; also elsewhere on the board
VCC2: A0.5, A1.5, PS2.2; also elsewhere on the board
VIN.PWR: JP2.17; also elsewhere on the board
VRR: A0.3, A1.3, A2.3, A3.3, A6.3, AOUT1.3, D2.3, D3.3, D4.3, D5.3, D6.3, DAC.V1.1, JP2.16, JTMP.1, PS3.2, Q2.S, VCC-VRR.P$1, VCC.RAIL.1, VCC.RAIL.2, VCC.RAIL.3
XBEE2.DO: H.X1.2; also elsewhere on the board
XBEE3.DI: H.X1.3; also elsewhere on the board
XBEE4: H.X1.4; also elsewhere on the board
XBEE5.RST: H.X1.5; also elsewhere on the board
XBEE7: H.X1.7
XBEE8: H.X1.8
XBEE9: H.X1.9; also elsewhere on the board
XBEE11: H.X2.10; also elsewhere on the board
XBEE12: H.X2.9; also elsewhere on the board
XBEE14: H.X2.7; also elsewhere on the board
XBEE15: H.X2.6; also elsewhere on the board
XBEE16: H.X2.5; also elsewhere on the board
XBEE17: H.X2.4; also elsewhere on the board
XBEE18: H.X2.3; also elsewhere on the board
XBEE19: H.X2.2; also elsewhere on the board
XBEE20: H.X2.1; also elsewhere on the board

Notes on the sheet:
MOSFET
DAC
Analog In only!!!
Prototype Shield
Pressure Sensor
Voltage divider to measure higher voltages
Analog in only!!!
Pull-downs
Dallas temp sensor
Vin divider
High voltage input
For normal input, use 0 ohm resistor

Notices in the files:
parts and their libraries:
SparkFun-Connectors: Licensing: Creative Commons ShareAlike 4.0 International - https://creativecommons.org/licenses/by-sa/4.0
